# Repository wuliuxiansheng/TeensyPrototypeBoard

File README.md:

TeensyPrototypeBoard
====================

Teensy Prototype Board including IMU, Bluetooth Low Energy module, SD card and OV camera module interface.

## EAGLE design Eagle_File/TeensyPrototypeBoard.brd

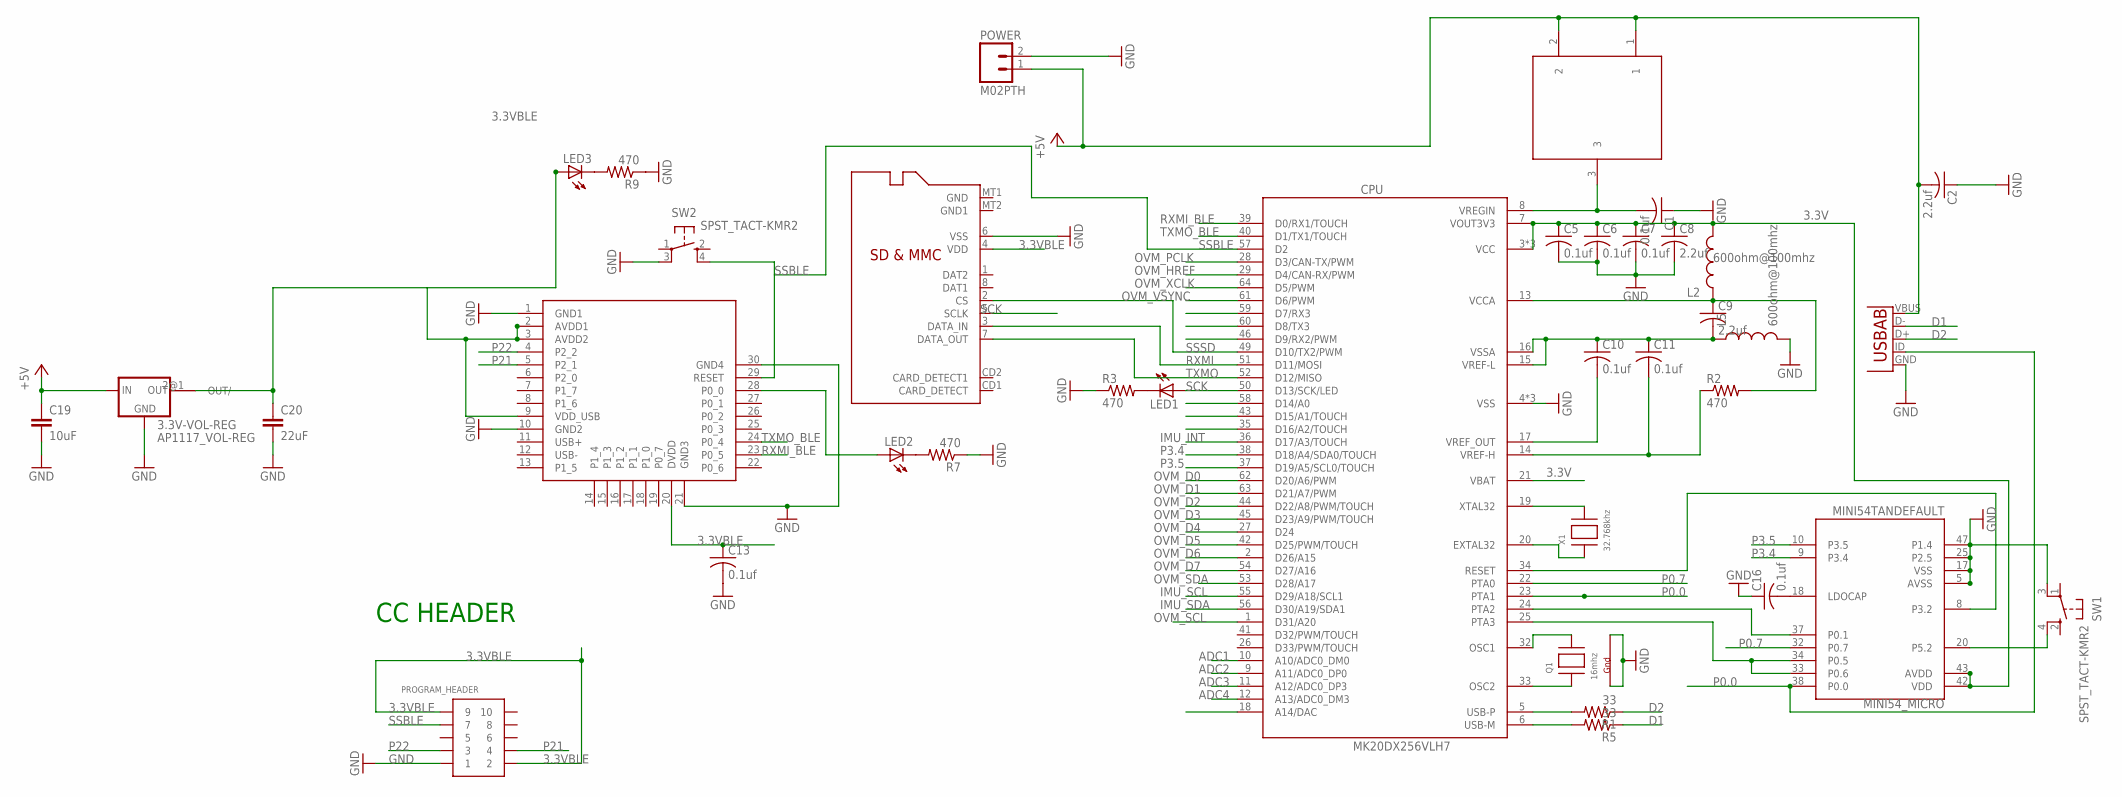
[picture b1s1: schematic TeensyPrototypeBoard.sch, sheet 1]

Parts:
3.3V-VOL-REG: AP1117_VOL-REG; SOT-89
C1, C5, C6, C7, C10, C11, C13, C16: 0.1uf; C0603
C2, C8, C9: 2.2uf; C0603
C19: 10uF; 0603-CAP
C20: 22uF; 0603-CAP
CPU: MK20DX256VLH7; QFP50P1200X1200X160-64N
L2, L5: 600ohm@100mhz; 0603
LED1, LED2, LED3: LEDCHIP-LED0603; CHIP-LED0603
MICRO_SD_CARD_SINK: MICROSD
MINI54_MICRO: MINI54TANDEFAULT; QFP50P900X900X160-48N
POWER: M02PTH; 1X02
PROGRAM_HEADER: CONN_5-2-FTSH-V; FTSH-105-DV
Q1: 16mhz; NX3225
R1, R5: 33; R0603
R2, R3, R7, R9: 470; R0603
SW1, SW2: SPST_TACT-KMR2; KMR2
U3: BLE112-A
U$4: PMEG4010CPA
USB: USB-AB; USB-AB-MICRO-SMD
X1: 32.768khz; XTAL3215

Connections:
3.3V: C5.1, C6.1, C7.1, C8.1, CPU.3 (VCC), CPU.7 (VOUT3V3), CPU.21 (VBAT), CPU.30 (VCC), CPU.48 (VCC), L2.2, MINI54_MICRO.42 (VDD), MINI54_MICRO.43 (AVDD)
3.3VBLE: 3.3V-VOL-REG.2 (OUT), C13.1, C20.1, LED3.A, MICRO_SD_CARD_SINK.4 (VDD), PROGRAM_HEADER.2, PROGRAM_HEADER.9, U3.2 (AVDD1), U3.3 (AVDD2), U3.9 (VDD_USB), U3.20 (DVDD); also elsewhere on the board
+5V: 3.3V-VOL-REG.3 (IN), C2.2, C19.1, POWER.1, U$4.1, U$4.2, USB.VBUS
ADC1: CPU.10 (A10/ADC0_DM0)
ADC2: CPU.9 (A11/ADC0_DP0)
ADC3: CPU.11 (A12/ADC0_DP3)
ADC4: CPU.12 (A13/ADC0_DM3)
D1: R5.1, USB.D-
D2: R1.1, USB.D+
GND: 3.3V-VOL-REG.1 (GND), C1.1, C2.1, C5.2, C6.2, C7.2, C8.2, C13.2, C16.1, C19.2, C20.2, CPU.4 (VSS), CPU.31 (VSS), CPU.47 (VSS), L5.2, MICRO_SD_CARD_SINK.6 (VSS), MINI54_MICRO.5 (AVSS), MINI54_MICRO.17 (VSS), MINI54_MICRO.25 (P2.5), MINI54_MICRO.47 (P1.4), POWER.2, PROGRAM_HEADER.1, Q1.2 (G2), Q1.4 (G1), R3.1, R7.1, R9.1, SW1.3 (P1), SW2.3 (P1), U3.1 (GND1), U3.10 (GND2), U3.21 (GND3), U3.30 (GND4), USB.GND; also elsewhere on the board
IMU_INT: CPU.36 (D17/A3/TOUCH); also elsewhere on the board
IMU_SCL: CPU.55 (D29/A18/SCL1); also elsewhere on the board
IMU_SDA: CPU.56 (D30/A19/SDA1); also elsewhere on the board
unnamed: CPU.19 (XTAL32), X1.P$2
unnamed: C1.2, CPU.8 (VREGIN), U$4.3
unnamed: C9.2, C10.1, C11.1, CPU.15 (VREF-L), CPU.16 (VSSA), L5.1
unnamed: C10.2, CPU.17 (VREF_OUT)
unnamed: C9.1, CPU.13 (VCCA), L2.1, R2.2
unnamed: C11.2, CPU.14 (VREF-H), R2.1
unnamed: CPU.20 (EXTAL32), X1.P$1
unnamed: CPU.32 (OSC1), Q1.3 (X2)
unnamed: CPU.33 (OSC2), Q1.1 (X1)
unnamed: CPU.5 (USB-P), R1.2
unnamed: CPU.6 (USB-M), R5.2
unnamed: LED1.C, R3.2
unnamed: CPU.34 (RESET), MINI54_MICRO.8 (P3.2)
unnamed: MINI54_MICRO.20 (P5.2), SW1.4 (S1)
unnamed: LED3.C, R9.2
unnamed: CPU.24 (PTA2), MINI54_MICRO.37 (P0.1)
unnamed: CPU.25 (PTA3), MINI54_MICRO.33 (P0.6), MINI54_MICRO.34 (P0.5)
unnamed: LED2.C, R7.2
unnamed: LED2.A, U3.28 (P0_0)
unnamed: C16.2, MINI54_MICRO.18 (LDOCAP)
OVM_D0: CPU.62 (D20/A6/PWM); also elsewhere on the board
OVM_D1: CPU.63 (D21/A7/PWM); also elsewhere on the board
OVM_D2: CPU.44 (D22/A8/PWM/TOUCH); also elsewhere on the board
OVM_D3: CPU.45 (D23/A9/PWM/TOUCH); also elsewhere on the board
OVM_D4: CPU.27 (D24); also elsewhere on the board
OVM_D5: CPU.42 (D25/PWM/TOUCH); also elsewhere on the board
OVM_D6: CPU.2 (D26/A15); also elsewhere on the board
OVM_D7: CPU.54 (D27/A16); also elsewhere on the board
OVM_HREF: CPU.29 (D4/CAN-RX/PWM); also elsewhere on the board
OVM_PCLK: CPU.28 (D3/CAN-TX/PWM); also elsewhere on the board
OVM_SCL: CPU.1 (D31/A20); also elsewhere on the board
OVM_SDA: CPU.53 (D28/A17); also elsewhere on the board
OVM_VSYNC: CPU.61 (D6/PWM); also elsewhere on the board
OVM_XCLK: CPU.64 (D5/PWM); also elsewhere on the board
P0.0: CPU.23 (PTA1), MINI54_MICRO.38 (P0.0), USB.ID (USBID)
P0.7: CPU.22 (PTA0), MINI54_MICRO.32 (P0.7)
P3.4: CPU.38 (D18/A4/SDA0/TOUCH), MINI54_MICRO.9 (P3.4)
P3.5: CPU.37 (D19/A5/SCL0/TOUCH), MINI54_MICRO.10 (P3.5)
P21: PROGRAM_HEADER.4, U3.5 (P2_1)
P22: PROGRAM_HEADER.3, U3.4 (P2_2)
RXMI: CPU.51 (D11/MOSI), MICRO_SD_CARD_SINK.3 (DATA_IN)
RXMI_BLE: CPU.39 (D0/RX1/TOUCH), U3.23 (P0_5)
SCK: CPU.50 (D13/SCK/LED), LED1.A, MICRO_SD_CARD_SINK.5 (SCLK)
SSBLE: CPU.57 (D2), PROGRAM_HEADER.7, SW2.4 (S1), U3.29 (RESET)
SSSD: CPU.49 (D10/TX2/PWM), MICRO_SD_CARD_SINK.2 (CS)
TXMO: CPU.52 (D12/MISO), MICRO_SD_CARD_SINK.7 (DATA_OUT)
TXMO_BLE: CPU.40 (D1/TX1/TOUCH), U3.24 (P0_4)

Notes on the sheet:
CC HEADER

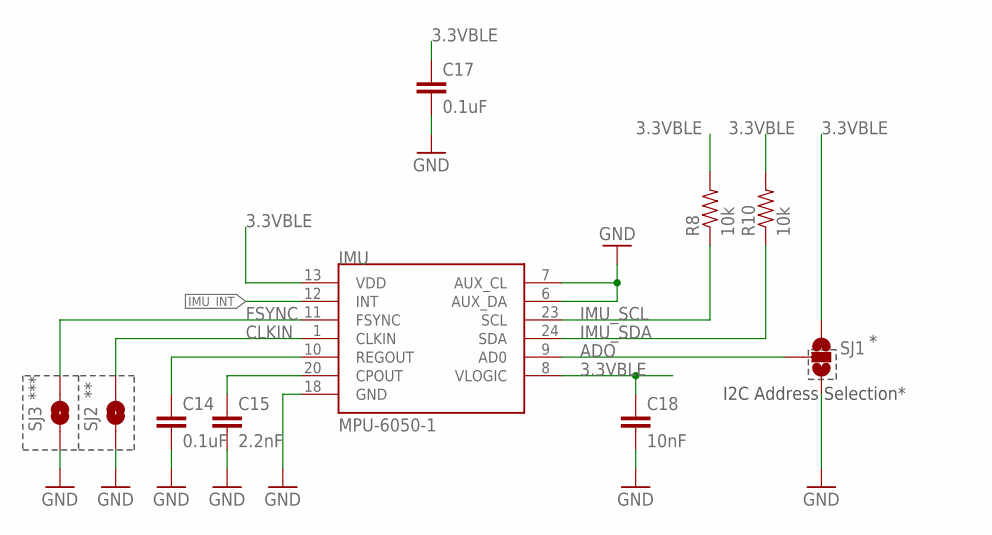
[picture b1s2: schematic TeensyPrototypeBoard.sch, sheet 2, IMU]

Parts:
C14, C17: 0.1uF; 0603-CAP
C15: 2.2nF; 0603-CAP
C18: 10nF; 0603-CAP
IMU: MPU-6050-1; QFN-24-4MM2
R8, R10: 10k; 0603-RES
SJ1: SOLDERJUMPER_2WAYPASTE2&3; SJ_3_PASTE2&3
SJ2, SJ3: SOLDERJUMPERTRACE; SJ_2S-TRACE

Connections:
3.3VBLE: C17.1, C18.1, IMU.8 (VLOGIC), IMU.13 (VDD), R8.2, R10.2, SJ1.1; also elsewhere on the board
ADO: IMU.9 (AD0), SJ1.2
CLKIN: IMU.1 (CLKIN), SJ2.2
FSYNC: IMU.11 (FSYNC), SJ3.2
GND: C14.2, C15.2, C17.2, C18.2, IMU.6 (AUX_DA), IMU.7 (AUX_CL), IMU.18 (GND), SJ1.3, SJ2.1, SJ3.1; also elsewhere on the board
IMU_INT: IMU.12 (INT); also elsewhere on the board
IMU_SCL: IMU.23 (SCL), R8.1; also elsewhere on the board
IMU_SDA: IMU.24 (SDA), R10.1; also elsewhere on the board
unnamed: C15.1, IMU.20 (CPOUT)
unnamed: C14.1, IMU.10 (REGOUT)

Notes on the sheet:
I2C Address Selection*
***

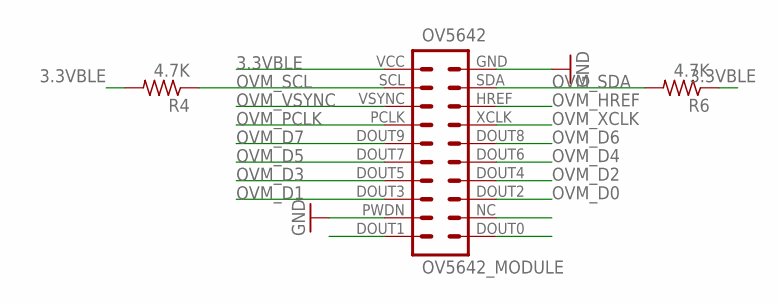
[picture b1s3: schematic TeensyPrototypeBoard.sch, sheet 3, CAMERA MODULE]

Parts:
OV5642: OV5642_MODULE
R4, R6: 4.7K; R0603

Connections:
3.3VBLE: OV5642.VCC (1), R4.2, R6.1; also elsewhere on the board
GND: OV5642.GND (2), OV5642.PWDN (17); also elsewhere on the board
OVM_D0: OV5642.DOUT2 (16); also elsewhere on the board
OVM_D1: OV5642.DOUT3 (15); also elsewhere on the board
OVM_D2: OV5642.DOUT4 (14); also elsewhere on the board
OVM_D3: OV5642.DOUT5 (13); also elsewhere on the board
OVM_D4: OV5642.DOUT6 (12); also elsewhere on the board
OVM_D5: OV5642.DOUT7 (11); also elsewhere on the board
OVM_D6: OV5642.DOUT8 (10); also elsewhere on the board
OVM_D7: OV5642.DOUT9 (9); also elsewhere on the board
OVM_HREF: OV5642.HREF (6); also elsewhere on the board
OVM_PCLK: OV5642.PCLK (7); also elsewhere on the board
OVM_SCL: OV5642.SCL (3), R4.1; also elsewhere on the board
OVM_SDA: OV5642.SDA (4), R6.2; also elsewhere on the board
OVM_VSYNC: OV5642.VSYNC (5); also elsewhere on the board
OVM_XCLK: OV5642.XCLK (8); also elsewhere on the board

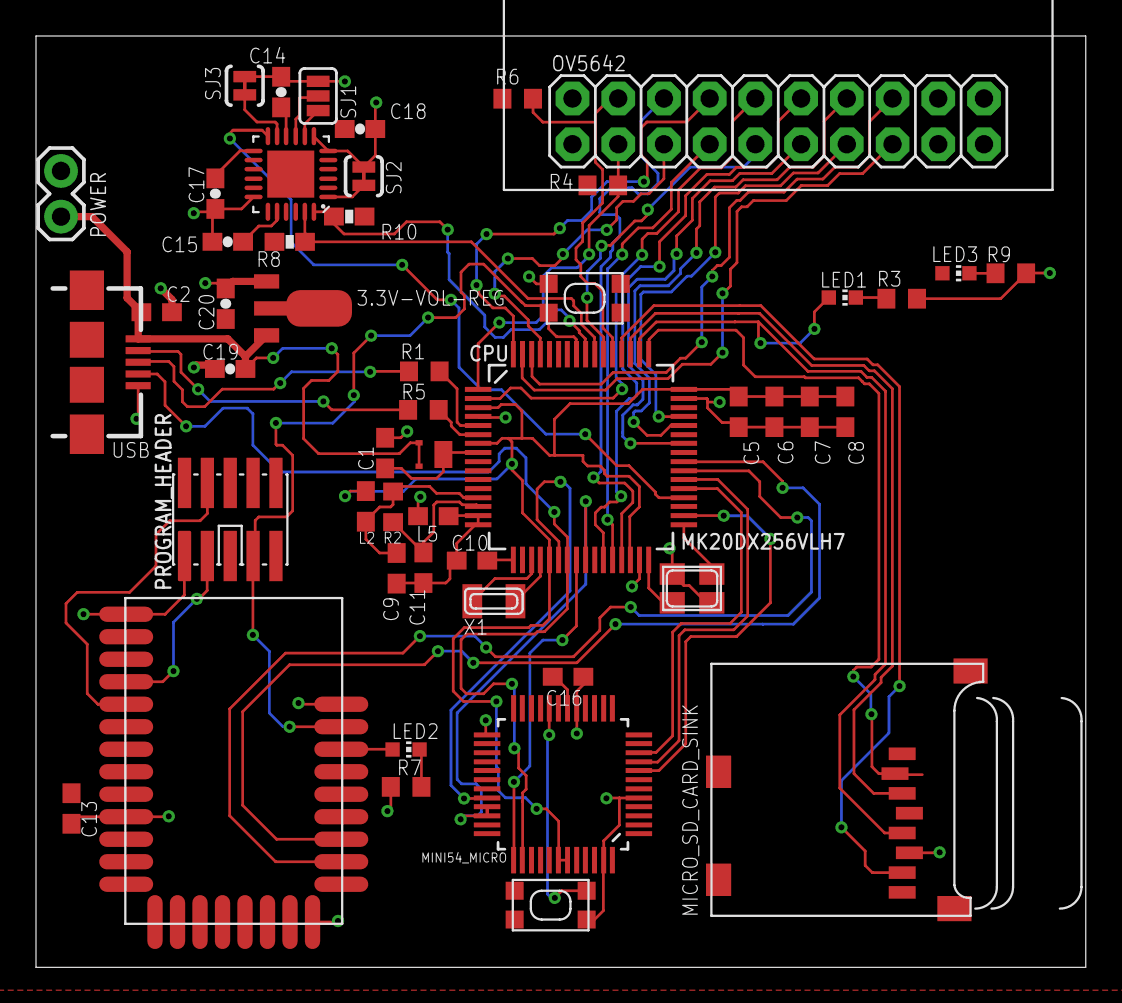
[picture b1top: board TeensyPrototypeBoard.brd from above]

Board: 2 copper layers, 58.3 x 51.7 mm, 50 parts (0 on the bottom side), 61 nets.

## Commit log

2014-07-28 add eagle files
2014-08-04 connect the oscillator and add generate BOM.txt
2014-08-09 move eagle files to Eagle_File folder
2014-08-09 add teensy 3.0 pin map file
2014-08-10 add datasheet for the micro on Teensy
2015-07-10 modify the name and value on the board

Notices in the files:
parts and their libraries:
SparkFun-Passives: Licensing: CC v3.0 Share-Alike You are welcome to use this library for commercial purposes.
